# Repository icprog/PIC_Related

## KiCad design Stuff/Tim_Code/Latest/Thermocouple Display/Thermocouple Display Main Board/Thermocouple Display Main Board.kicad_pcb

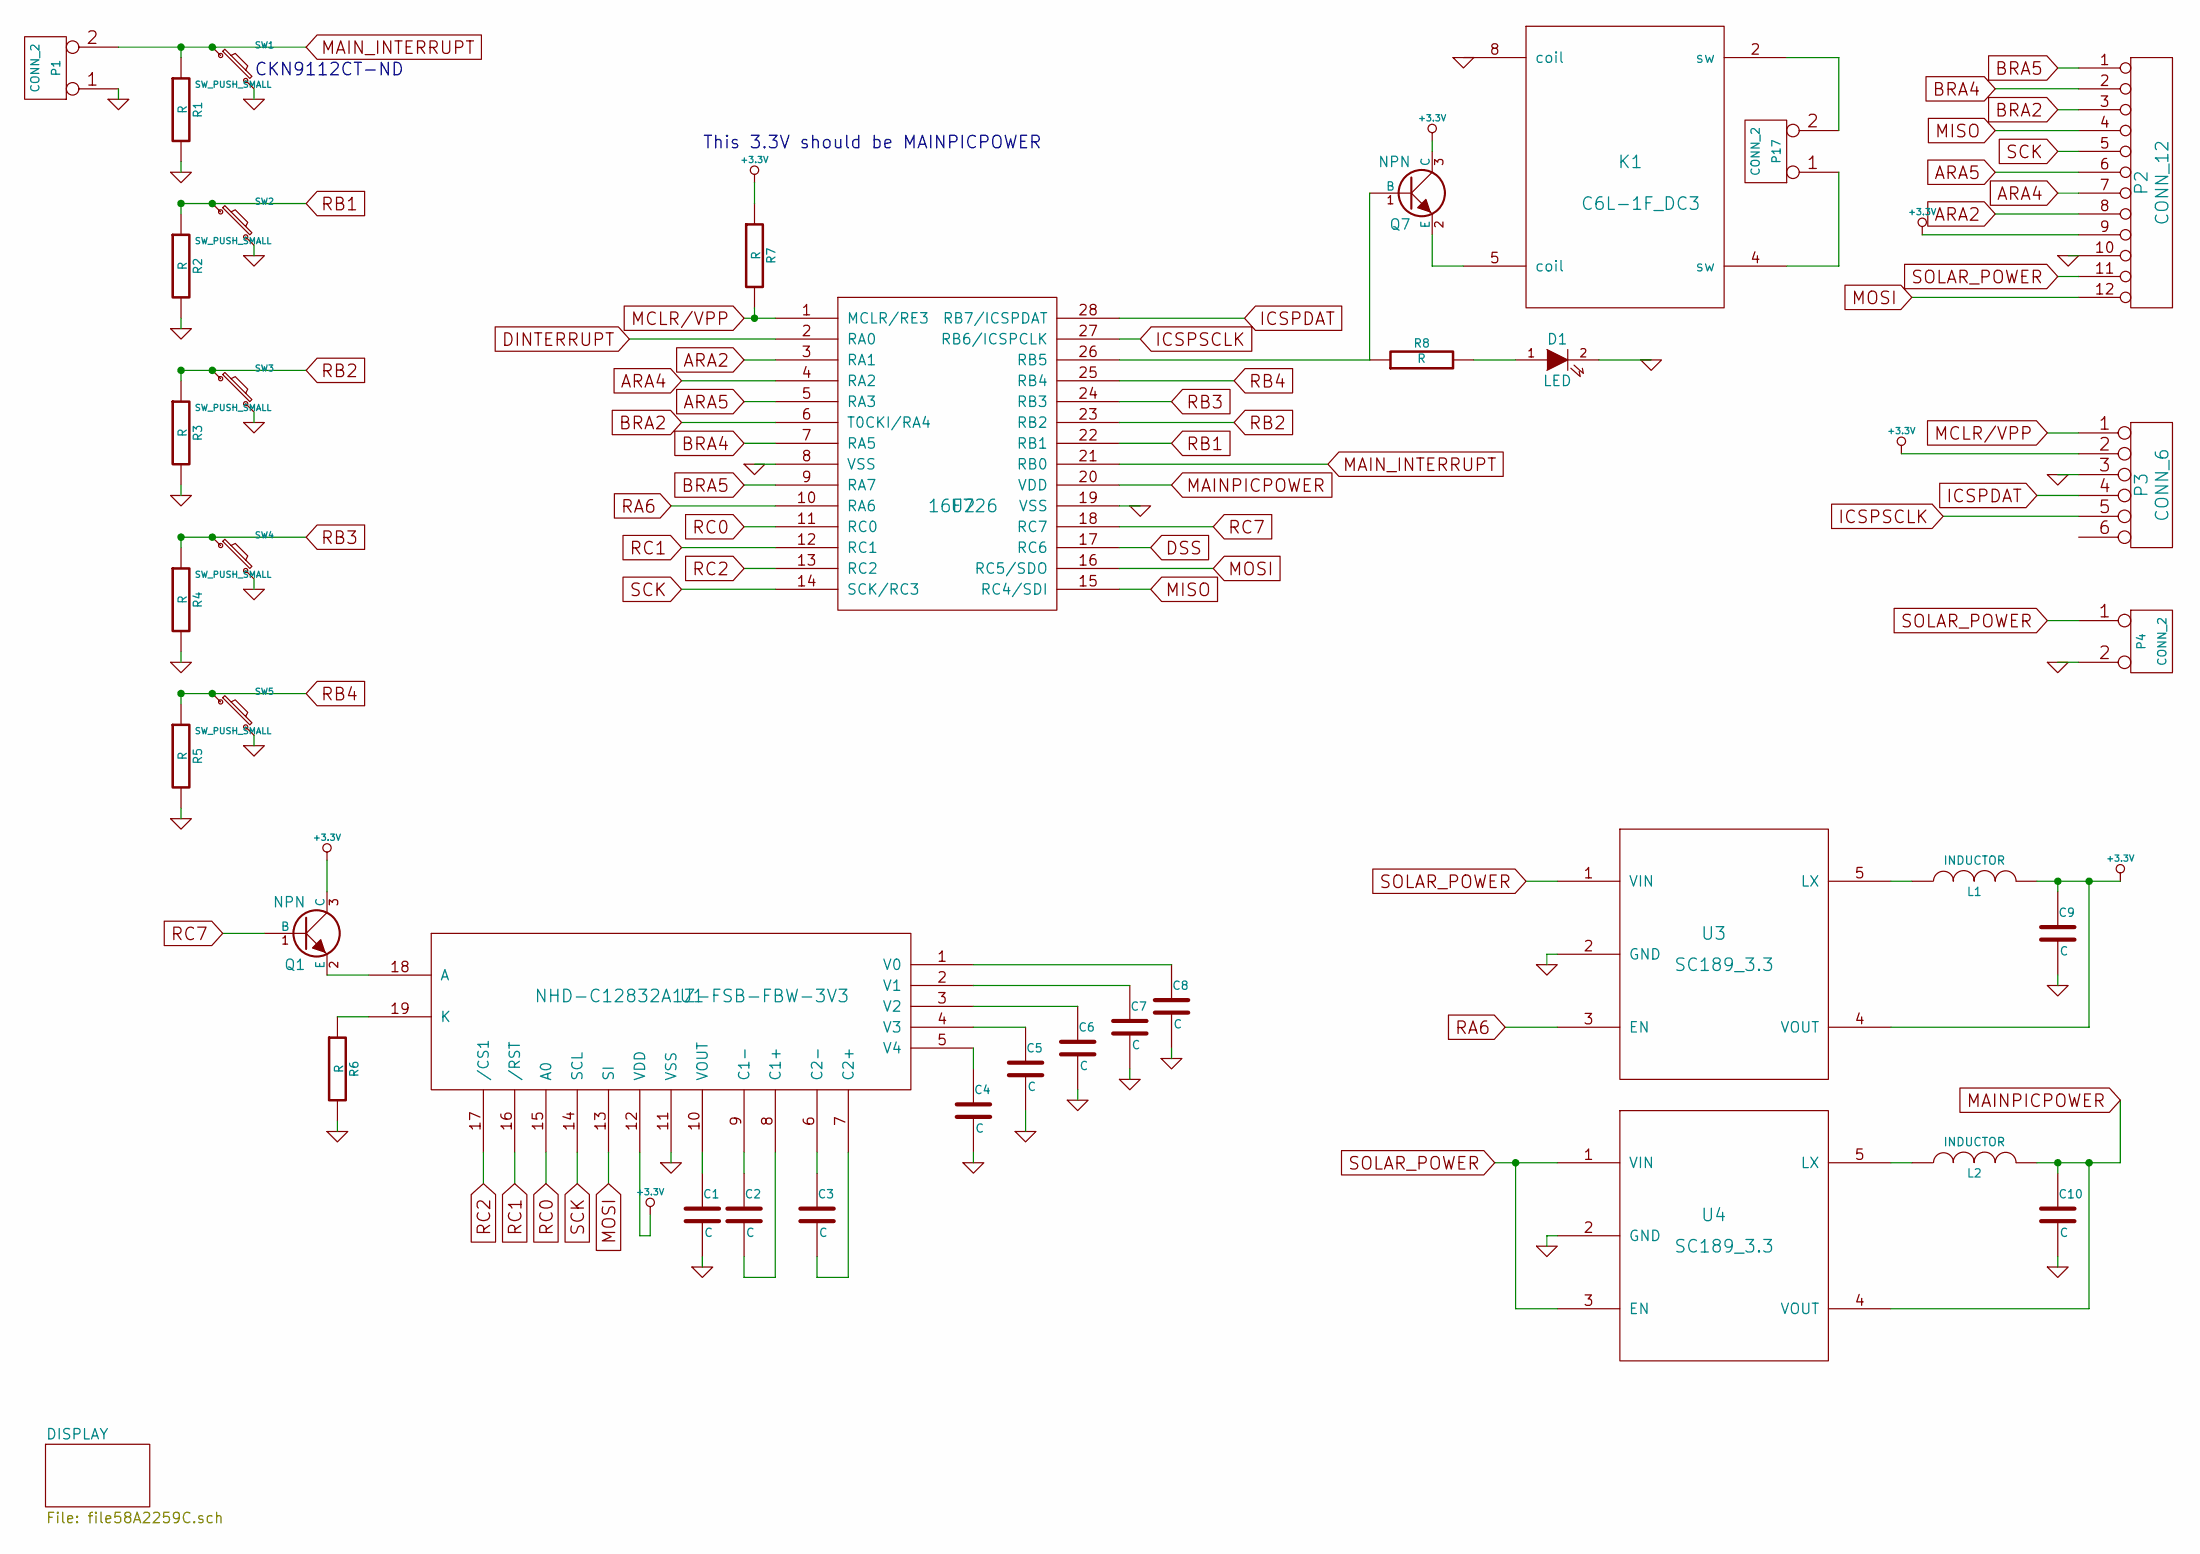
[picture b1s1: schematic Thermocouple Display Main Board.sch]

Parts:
C1, C2, C3, C4, C5, C6, C7, C8, C9, C10: C
D1: LED
K1: C6L-1F_DC3
L1, L2: INDUCTOR
P1, P4, P17: CONN_2
P2: CONN_12
P3: CONN_6
Q1, Q7: NPN
R1, R2, R3, R4, R5, R6, R7, R8: R
SW1, SW2, SW3, SW4, SW5: SW_PUSH_SMALL
U1: NHD-C12832A1Z-FSB-FBW-3V3
U2: 16F726
U3, U4: SC189_3.3

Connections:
+3.3V: C9.1, L1.2, P2.9, P3.2, Q1.3 (C), Q7.3 (C), R7.1, U1.12 (VDD), U3.4 (VOUT); also elsewhere on the board
ARA2: P2.8, U2.3 (RA1)
ARA4: P2.7, U2.4 (RA2)
ARA5: P2.6, U2.5 (RA3)
BRA2: P2.3, U2.6 (T0CKI/RA4)
BRA4: P2.2, U2.7 (RA5)
BRA5: P2.1, U2.9 (RA7)
DINTERRUPT: U2.2 (RA0); also elsewhere on the board
DSS: U2.17 (RC6); also elsewhere on the board
GND: C1.2, C4.2, C5.2, C6.2, C7.2, C8.2, C9.2, C10.2, D1.2 (K), K1.8 (coil), P1.1, P2.10, P3.3, P4.2 (PM), R1.2, R2.2, R3.2, R4.2, R5.2, R6.2, SW1.2, SW2.2, SW3.2, SW4.2, SW5.2, U1.11 (VSS), U2.8 (VSS), U2.19 (VSS), U3.2 (GND), U4.2 (GND); also elsewhere on the board
ICSPDAT: P3.4, U2.28 (RB7/ICSPDAT)
ICSPSCLK: P3.5, U2.27 (RB6/ICSPCLK)
MAINPICPOWER: C10.1, L2.2, U2.20 (VDD), U4.4 (VOUT)
MAIN_INTERRUPT: P1.2 (PM), R1.1, SW1.1, U2.21 (RB0)
MCLR/VPP: P3.1, R7.2, U2.1 (MCLR/RE3)
MISO: P2.4, U2.15 (RC4/SDI); also elsewhere on the board
MOSI: P2.12, U1.13 (SI), U2.16 (RC5/SDO); also elsewhere on the board
unnamed: C2.1, U1.9 (C1-)
unnamed: C1.1, U1.10 (VOUT)
unnamed: C4.1, U1.5 (V4)
unnamed: C5.1, U1.4 (V3)
unnamed: C6.1, U1.3 (V2)
unnamed: C8.1, U1.1 (V0)
unnamed: C7.1, U1.2 (V1)
unnamed: R6.1, U1.19 (K)
unnamed: Q1.2 (E), U1.18 (A)
unnamed: C3.2, U1.7 (C2+)
unnamed: C3.1, U1.6 (C2-)
unnamed: C2.2, U1.8 (C1+)
unnamed: L2.1, U4.5 (LX)
unnamed: D1.1 (A), R8.2
unnamed: Q7.1 (B), R8.1, U2.26 (RB5)
unnamed: K1.2 (sw), P17.2 (PM)
unnamed: K1.4 (sw), P17.1
unnamed: K1.5 (coil), Q7.2 (E)
unnamed: L1.1, U3.5 (LX)
RA6: U2.10 (RA6), U3.3 (EN)
RB1: R2.1, SW2.1, U2.22 (RB1)
RB2: R3.1, SW3.1, U2.23 (RB2)
RB3: R4.1, SW4.1, U2.24 (RB3)
RB4: R5.1, SW5.1, U2.25 (RB4)
RC0: U1.15 (A0), U2.11 (RC0)
RC1: U1.16 (/RST), U2.12 (RC1)
RC2: U1.17 (/CS1), U2.13 (RC2)
RC7: Q1.1 (B), U2.18 (RC7)
SCK: P2.5, U1.14 (SCL), U2.14 (SCK/RC3); also elsewhere on the board
SOLAR_POWER: P2.11, P4.1, U3.1 (VIN), U4.1 (VIN), U4.3 (EN)

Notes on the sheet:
CKN9112CT-ND
This 3.3V should be MAINPICPOWER

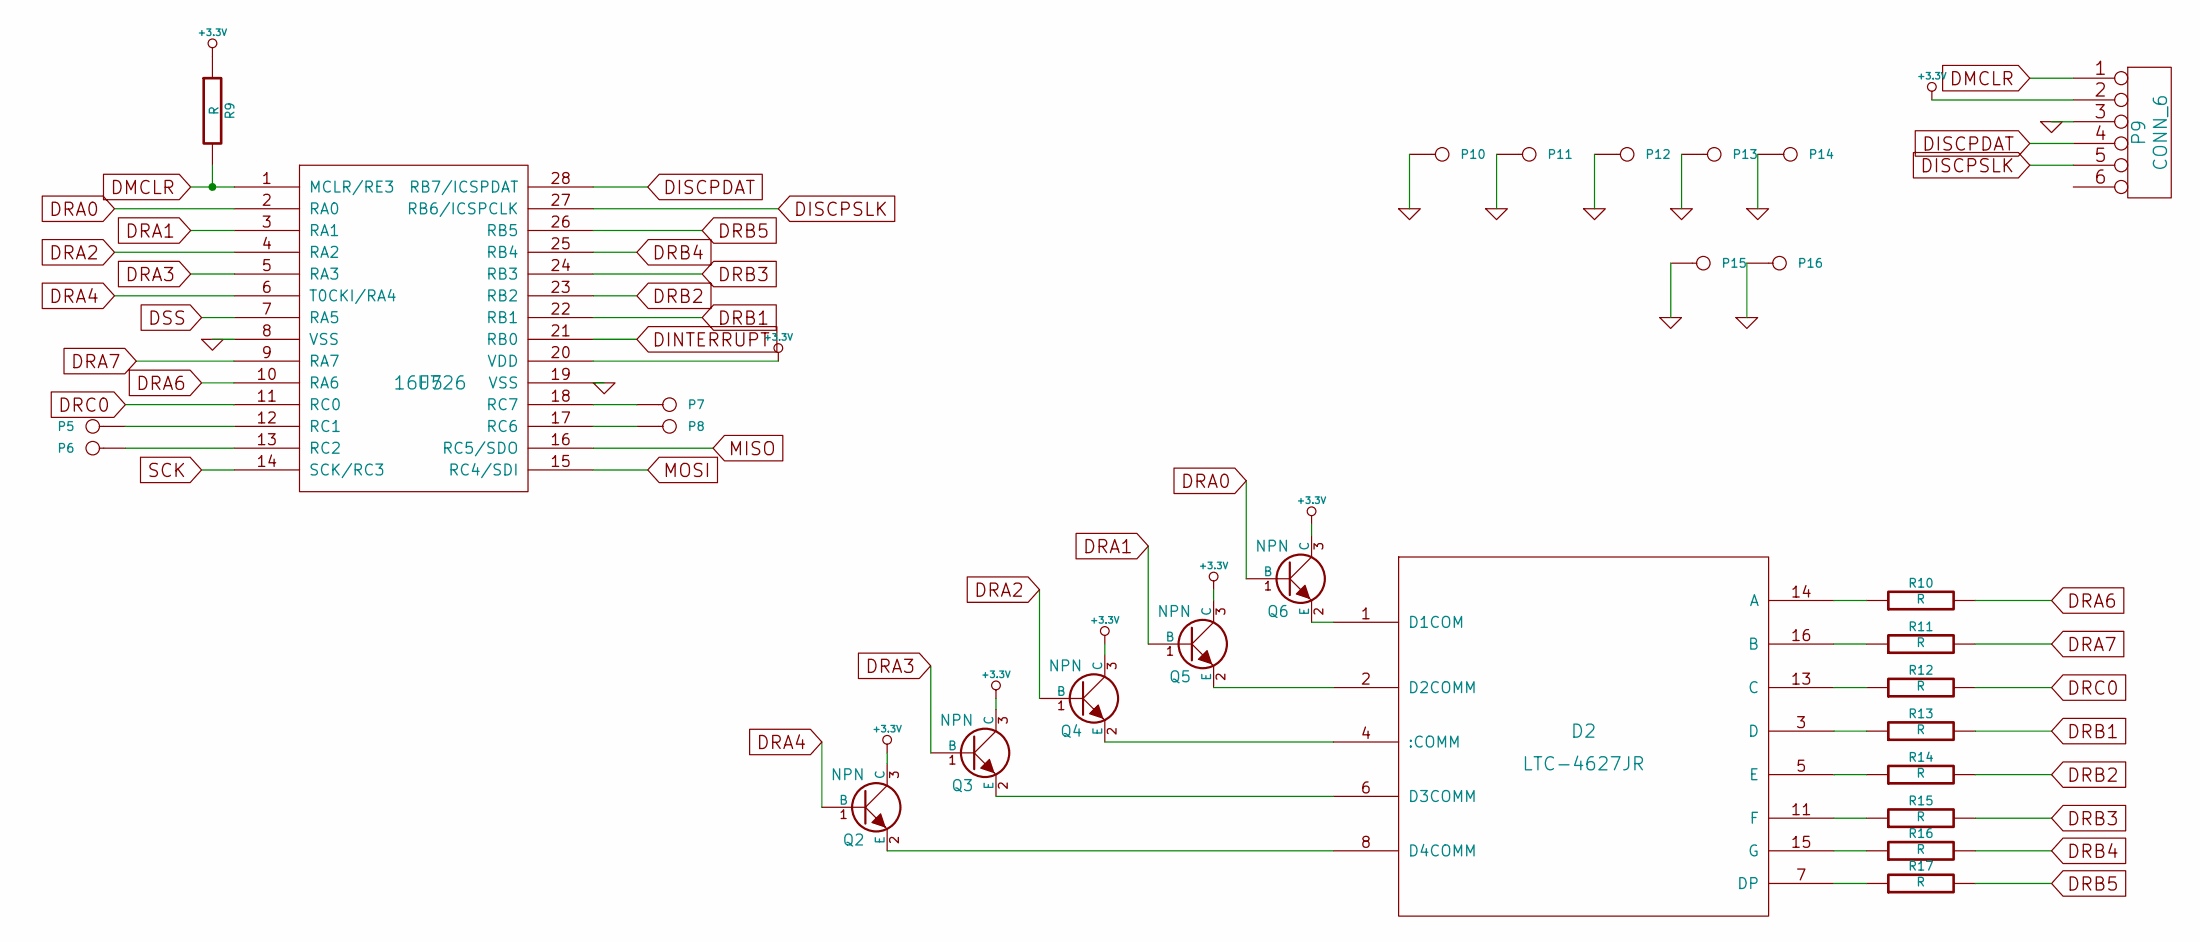
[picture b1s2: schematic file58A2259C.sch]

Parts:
D2: LTC-4627JR
P5, P6, P7, P8, P10, P11, P12, P13, P14, P15, P16: CONN_1
P9: CONN_6
Q2, Q3, Q4, Q5, Q6: NPN
R9, R10, R11, R12, R13, R14, R15, R16, R17: R
U5: 16F726

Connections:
+3.3V: P9.2, Q2.3 (C), Q3.3 (C), Q4.3 (C), Q5.3 (C), Q6.3 (C), R9.1, U5.20 (VDD); also elsewhere on the board
DINTERRUPT: U5.21 (RB0); also elsewhere on the board
DISCPDAT: P9.4, U5.28 (RB7/ICSPDAT)
DISCPSLK: P9.5, U5.27 (RB6/ICSPCLK)
DMCLR: P9.1, R9.2, U5.1 (MCLR/RE3)
DRA0: Q6.1 (B), U5.2 (RA0)
DRA1: Q5.1 (B), U5.3 (RA1)
DRA2: Q4.1 (B), U5.4 (RA2)
DRA3: Q3.1 (B), U5.5 (RA3)
DRA4: Q2.1 (B), U5.6 (T0CKI/RA4)
DRA6: R10.2, U5.10 (RA6)
DRA7: R11.2, U5.9 (RA7)
DRB1: R13.2, U5.22 (RB1)
DRB2: R14.2, U5.23 (RB2)
DRB3: R15.2, U5.24 (RB3)
DRB4: R16.2, U5.25 (RB4)
DRB5: R17.2, U5.26 (RB5)
DRC0: R12.2, U5.11 (RC0)
DSS: U5.7 (RA5); also elsewhere on the board
GND: P9.3, P10.1, P11.1, P12.1, P13.1, P14.1, P15.1, P16.1, U5.8 (VSS), U5.19 (VSS); also elsewhere on the board
MISO: U5.16 (RC5/SDO); also elsewhere on the board
MOSI: U5.15 (RC4/SDI); also elsewhere on the board
unnamed: D2.15 (G), R16.1
unnamed: D2.7 (DP), R17.1
unnamed: D2.11 (F), R15.1
unnamed: D2.5 (E), R14.1
unnamed: D2.3 (D), R13.1
unnamed: D2.13 (C), R12.1
unnamed: D2.14 (A), R10.1
unnamed: D2.16 (B), R11.1
unnamed: P8.1, U5.17 (RC6)
unnamed: P5.1, U5.12 (RC1)
unnamed: P6.1, U5.13 (RC2)
unnamed: P7.1, U5.18 (RC7)
unnamed: D2.4 (:COMM), Q4.2 (E)
unnamed: D2.6 (D3COMM), Q3.2 (E)
unnamed: D2.8 (D4COMM), Q2.2 (E)
unnamed: D2.2 (D2COMM), Q5.2 (E)
unnamed: D2.1 (D1COM), Q6.2 (E)
SCK: U5.14 (SCK/RC3); also elsewhere on the board

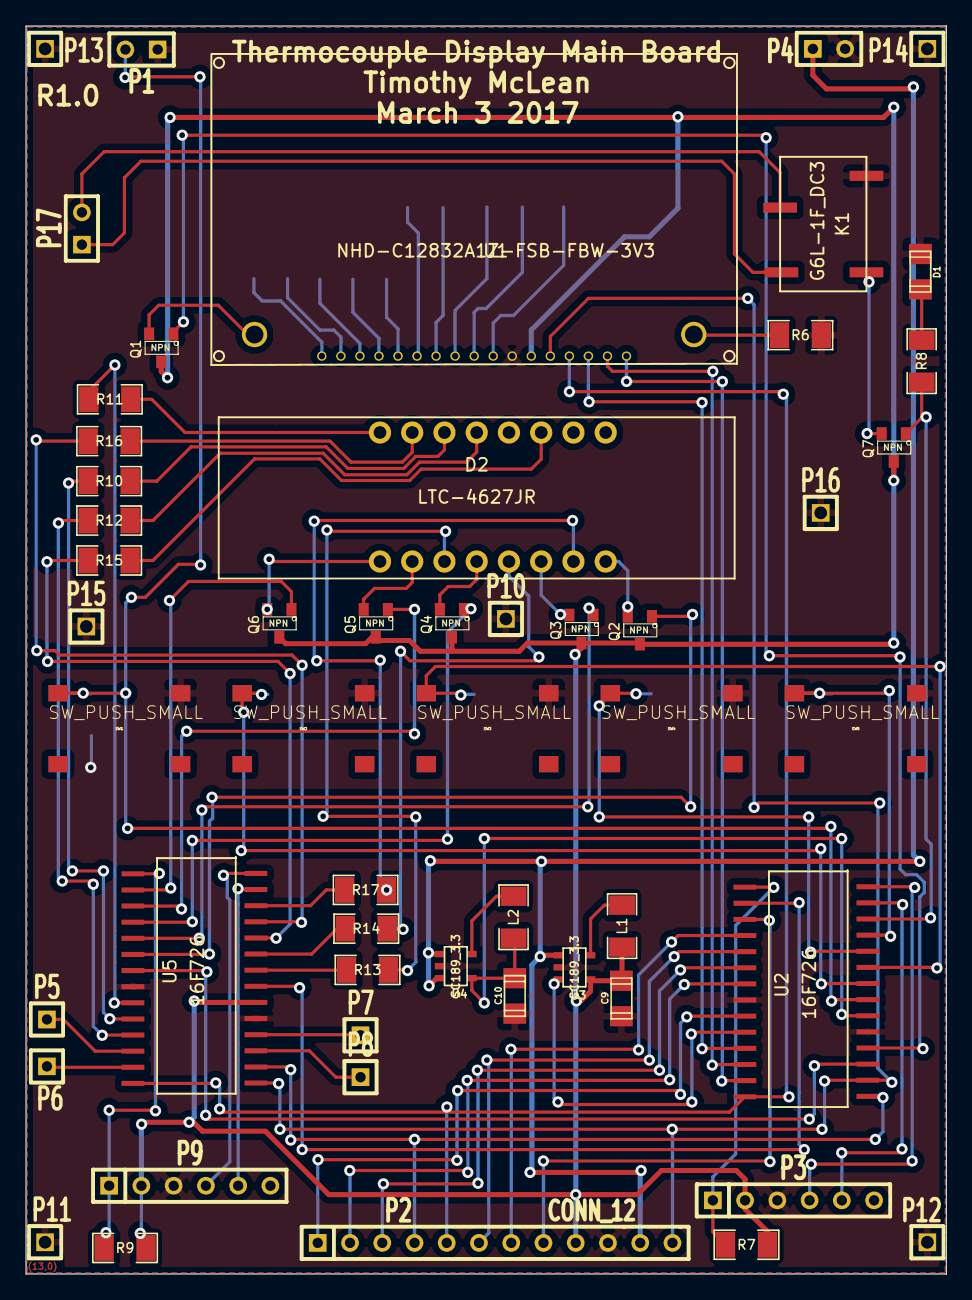
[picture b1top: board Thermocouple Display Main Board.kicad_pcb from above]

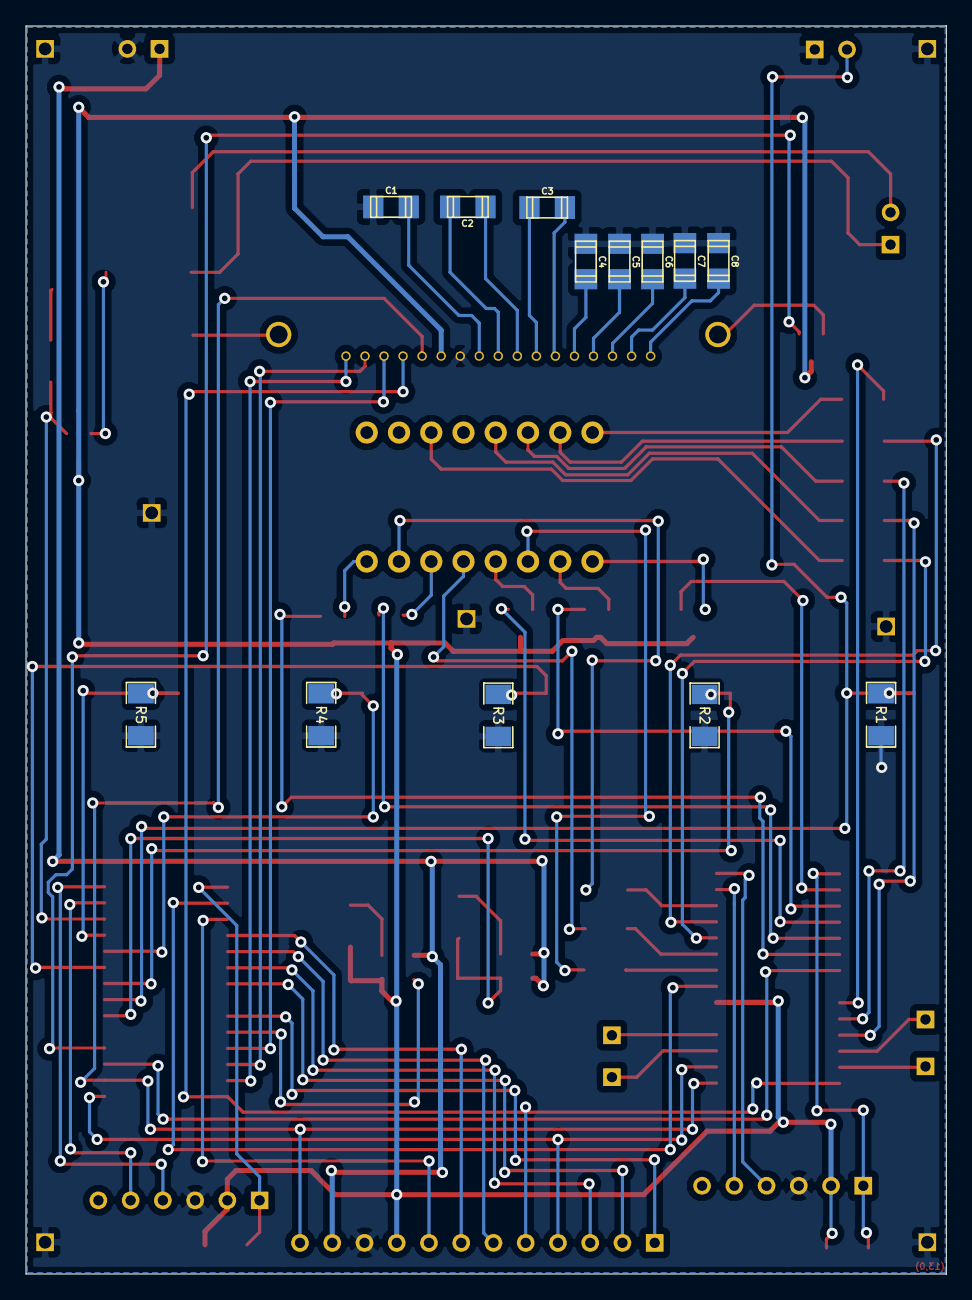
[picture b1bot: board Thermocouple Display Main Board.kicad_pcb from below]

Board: 2 copper layers, 72.5 x 98.3 mm, 66 parts (13 on the bottom side), 80 nets.

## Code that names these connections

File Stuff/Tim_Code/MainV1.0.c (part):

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void (display_ADC_count_on_LEDs)(int temp){
    
if (temp > 150){
    RB0 = 1;
} 
else RB0 = 0;

if (temp > 300){
    RB1 = 1;
} 
else RB1 = 0;

if (temp > 450){
    RB2 = 1;
} 
else RB2 = 0;

if (temp > 600){
    RB3 = 1;
} 
else RB3 = 0;

if (temp > 750){
    RB4 = 1;
} 
else RB4 = 0;    
    
if (temp > 1000){
//    RB5 = 1;
} 
//else RB5 = 0;    
    
    
    
}
void display_temperature_on_LEDs(float temp){
if (temp > 200){
    RB0 = 1;
} 
else RB0 = 0;

if (temp > 220){
    RB1 = 1;
} 
else RB1 = 0;

if (temp > 240){
    RB2 = 1;
} 
else RB2 = 0;

if (temp > 260){
    RB3 = 1;
} 
else RB3 = 0;

if (temp > 280){
    RB4 = 1;
} 
else RB4 = 0;    
    
if (temp > 300){
//    RB5 = 1;
} 
//else RB5 = 0;    
    
    
    
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
void display_temperature_on_LEDs2(float temp){
if (temp > 230){
    RB0 = 1;
} 
else RB0 = 0;

if (temp > 240){
    RB1 = 1;
} 
else RB1 = 0;

if (temp > 250){
    RB2 = 1;
} 
else RB2 = 0;

if (temp > 260){
    RB3 = 1;
} 
else RB3 = 0;

if (temp > 270){
    RB4 = 1;
} 
else RB4 = 0;    
    
if (temp > 280){
//    RB5 = 1;
} 
//else RB5 = 0;    
    
    
    
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    char dummy_char = 0;
    temp = temp / 10;
    byte_1 = (char) temp;
//   RC0 = 0; 
   __delay_us(100);
   dummy_char = (SPI_TRANSFER)(byte_1);
   __delay_us(100);
//   RC0 = 1;


}
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    
    //Beginning of RA4 input Switch debounce code
    if ((RA4 == 0) && (button_array[0][3] == 0)){  //0 equals button depressed and button_array[0][3] is for off bit latch
        button_array[0][2] = 1; //[x][y] x = switch 1(RA4) y = on bit active (switch one latched or active)
    }
    if (button_array[0][2] == 1){
        button_array[0][0]++;   //[x][y] x = switch 1(RA4) y = latched on timer
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        }
    }
    if ((button_array[0][0] > 5) && (RA4 == 1)){ //check if latched on timer has expired and button no longer depressed
        button_array[0][2] = 0; //turn off active button depression for RA4
        button_array[0][0] = 0; //reset latch on timer
        button_array[0][3] = 1; //[x][y] x = switch 1(RA4) y = off bit active (switch one not active)
        button_array[0][1] = 0; //reset off timer        
    }
    if (button_array[0][3] == 1){
        button_array[0][1]++;   //increment button off timer
    }
    if (button_array[0][1] > 5){
        button_array[0][3] = 0; //[x][y] x = switch 1(RA4) y = off bit active (switch one not active)
    }
//End of RA4 Switch debounce code

    //Beginning of RA5 input Switch debounce code
    if ((RA5 == 0) && (button_array[1][3] == 0)){  //0 equals button depressed and button_array[0][3] is for off bit latch
        button_array[1][2] = 1; //[x][y] x = switch 2(RA5) y = on bit active (switch one latched or active)
    }
    if (button_array[1][2] == 1){
        button_array[1][0]++;   //[x][y] x = switch 2(RA5) y = latched on timer
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        }
    }
    if ((button_array[1][0] > 5) && (RA5 == 1)){ //check if latched on timer has expired and button no longer depressed
        button_array[1][2] = 0; //turn off active button depression for RA4
        button_array[1][0] = 0; //reset latch on timer
        button_array[1][3] = 1; //[x][y] x = switch 2(RA5) y = off bit active (switch one not active)
        button_array[1][1] = 0; //reset off timer        
    }
    if (button_array[1][3] == 1){
        button_array[1][1]++;   //increment button off timer
    }
    if (button_array[1][1] > 5){
        button_array[1][3] = 0; //[x][y] x = switch 2(RA5) y = off bit active (switch one not active)
    }
//End of RA5 Switch debounce code
    
    //Beginning of RA7 input Switch debounce code
    if ((RA7 == 0) && (button_array[2][3] == 0)){  //0 equals button depressed and button_array[0][3] is for off bit latch
        button_array[2][2] = 1; //[x][y] x = switch 3(RA7) y = on bit active (switch one latched or active)
    }
    if (button_array[2][2] == 1){
        button_array[2][0]++;   //[x][y] x = switch 3(RA7) y = latched on timer
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        }
    }
    if ((button_array[2][0] > 10) && (RA7 == 1)){ //check if latched on timer has expired and button no longer depressed
        button_array[2][2] = 0; //turn off active button depression for RA7
        button_array[2][0] = 0; //reset latch on timer
        button_array[2][3] = 1; //[x][y] x = switch 3(RA7) y = off bit active (switch one not active)
        button_array[2][1] = 0; //reset off timer        
    }
    if (button_array[2][3] == 1){
        button_array[2][1]++;   //increment button off timer
    }
    if (button_array[2][1] > 10){
        button_array[2][3] = 0; //[x][y] x = switch 3(RA7) y = off bit active (switch one not active)
    }
//End of RA5 Switch debounce code


    if (button_array[2][2] == 1){
        RB4 = 1;
    }
    else RB4 = 0;
    
    
    
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void set_alarm_point(void){
 
    if (button_array[0][2] == 1){   //check button RA4
        RC0 = 0;
        __delay_us(100);
        format_temp_to_send(H_alarm_point_array[0][0]);
        RC0 = 1;
        __delay_us(100);
        if ((button_array[1][2] == 1) && (H_alarm_point_array[0][2] < 1)){
            H_alarm_point_array[0][0] = H_alarm_point_array[0][0] + 10; //10 is equal to 1 degree
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IO_Initialize();
spi_init();
ADCC_Initialize();
RC7 = 1;    //Thermistor power    
while (1){
    program_cycles++;
    
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        RB5 = 1 - RB5;  //toggle LED
        program_cycles = 0;
    }
 //   RC7 = 1;    //Thermistor power
//    temp0 = ADCRead(3);
//     temp0 = 1023 - temp0;
//    temp_in_degree_C = tempCalc(temp0);
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        final_temps[0] = average_temps(temp_array0);
    }
    if ((program_cycles == 50) && (button_array[0][2] == 0)){
        RC0 = 0;    //SS for Display 0
         __delay_us(80);
        format_temp_to_send(final_temps[0]);
        RC0 = 1;    //SS for Display 0
        __delay_us(80);
    }
    if (program_cycles == 60){
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        final_temps[1] = average_temps(temp_array1);
    }
    if (program_cycles == 100){
        RC1 = 0;    //SS for Display 1
        __delay_us(80);
        format_temp_to_send(final_temps[1]);
        RC1 = 1;    //SS for Display 1
         __delay_us(80);
    }
    if (program_cycles == 110){
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        final_temps[2] = average_temps(temp_array2);
    }
    if (program_cycles == 150){
        RC2 = 0;    //SS for Display 2
        __delay_us(80);
        format_temp_to_send(final_temps[2]);
        RC2 = 1;    //SS for Display 2
         __delay_us(80);
    }
    if (program_cycles == 160){
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        final_temps[3] = average_temps(temp_array3);
    }
    if (program_cycles == 200){
        RC6 = 0;    //SS for Display 3
         __delay_us(80);
        format_temp_to_send(final_temps[3]);
        RC6 = 1;    //SS for Display 3
         __delay_us(80);
    }

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//    display_ADC_count_on_LEDs(temp0);
//    display_temperature_on_LEDs2(temp_in_degree_C);
//    display_temperature_on_LEDs2(final_temps[0]);
//   RC0 = 0; 
//   __delay_us(100);
//   test_char = (SPI_TRANSFER)('U');
//   __delay_us(100);
//   RC0 = 1;
//   if (test_char == 'U'){
//       RB5 = 1;
//   }
//   else RB5 = 0;
//   __delay_us(10000);
//   __delay_us(10000);
//    RB0 = 0;
//    RB1 = 0;
//    RB2 = 0;
//    RB3 = 0;
//    RB4 = 0;
//    RB5 = 1;
        
   
}
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
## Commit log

2018-09-13 Initial Commit, Transferred to New Repo
    GitHub fucked up, kept erroring out, transferred all to new Repo, hope it fixes problem
2018-09-13 Initial Commit New Repo
2018-09-13 Temporary Show Faults on display
2018-09-13 KS0108 Stuff
2018-09-14 Fixed GroupHead Temperature control, now holds within .2 DegF
2018-09-14 Cleanup main display
2018-09-14 Charger Tuning
2018-09-14 n
    n
2018-09-14 GitIgnore Update
2018-09-14 Remove
2018-09-14 Git Ignore Update
